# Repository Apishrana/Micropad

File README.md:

# Macropad

This is my macropad that i am gonna be using to increase my productivity,
[Design link](https://www.tldraw.com/f/6q5K0vjcdTGi3-sUILjF2?d=v49.-201.1104.759.page)

## Why i made this

This macropad have all the shortcuts that I commonly use in my coding and research these are located on left side of the macropad, on the right side I have music control and display I am gonna be using it on study sessions so i don't have to look on my screen to control music

## Project images

### Full assembly

### PCB

### Schematic

## BOM

check [BOM](./BOM.csv)

## Author

Created by [ApishRana](https://github.com/ApishRana)

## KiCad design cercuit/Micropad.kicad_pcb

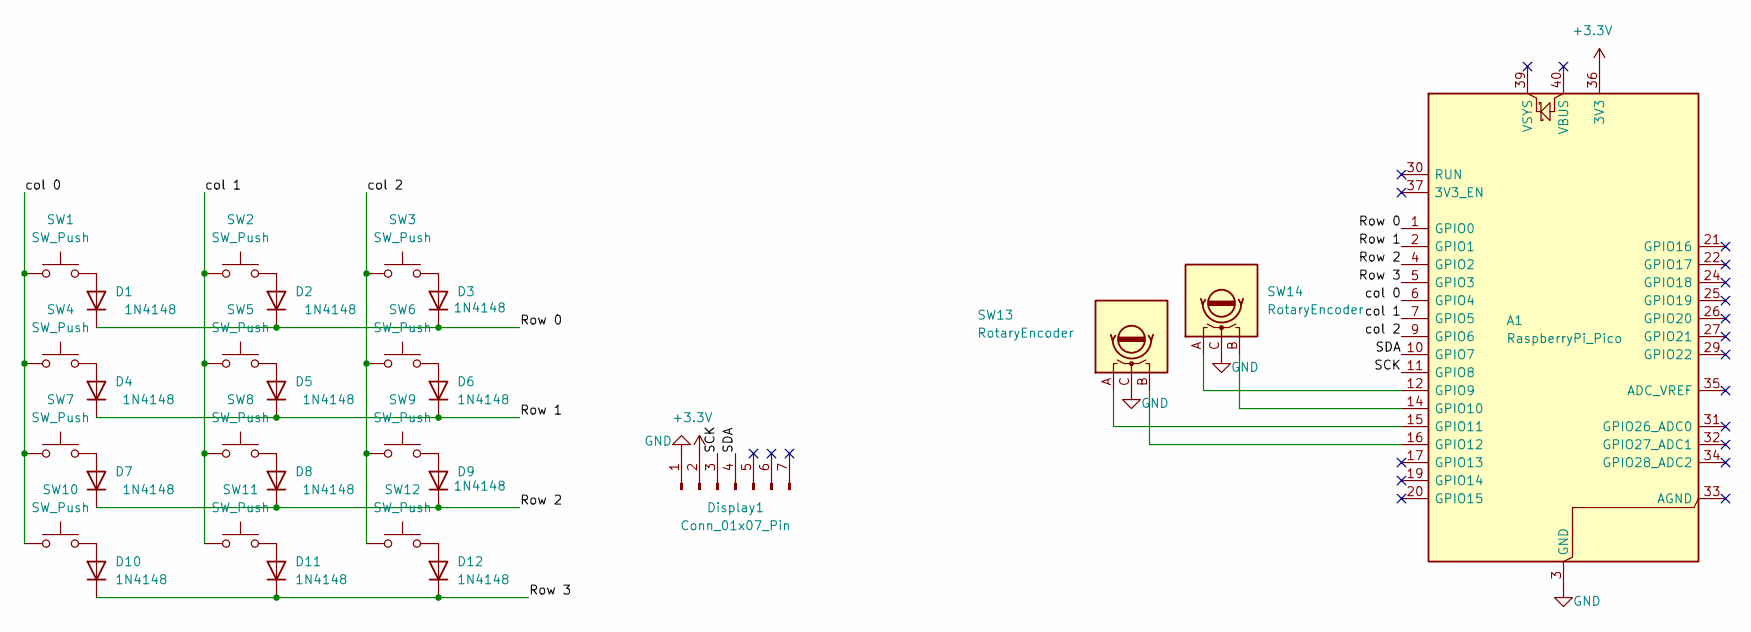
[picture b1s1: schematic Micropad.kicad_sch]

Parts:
A1: RaspberryPi_Pico; RaspberryPi_Pico_Common_THT
D1, D2, D3, D4, D5, D6, D7, D8, D9, D10, D11, D12: 1N4148; D_DO-35_SOD27_P7.62mm_Horizontal
Display1: Conn_01x07_Pin; 128x64OLED
SW1, SW2, SW3, SW4, SW5, SW6, SW7, SW8, SW9, SW10, SW11, SW12: SW_Push; SW_Cherry_MX_1.00u_PCB
SW13, SW14: RotaryEncoder; RotaryEncoder_Alps_EC11E-Switch_Vertical_H20mm

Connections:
+3.3V: A1.36 (3V3), Display1.2
/Row 0: A1.1 (GPIO0), D1.1 (K), D2.1 (K), D3.1 (K)
/Row 1: A1.2 (GPIO1), D4.1 (K), D5.1 (K), D6.1 (K)
/Row 2: A1.4 (GPIO2), D7.1 (K), D8.1 (K), D9.1 (K)
/Row 3: A1.5 (GPIO3), D10.1 (K), D11.1 (K), D12.1 (K)
/SCK: A1.11 (GPIO8), Display1.3
/SDA: A1.10 (GPIO7), Display1.4
/col 0: A1.6 (GPIO4), SW1.1, SW4.1, SW7.1, SW10.1
/col 1: A1.7 (GPIO5), SW2.1, SW5.1, SW8.1, SW11.1
/col 2: A1.9 (GPIO6), SW3.1, SW6.1, SW9.1, SW12.1
GND: A1.3 (GND), A1.8 (GND), A1.13 (GND), A1.18 (GND), A1.23 (GND), A1.28 (GND), A1.38 (GND), Display1.1, SW13.C, SW14.C
unnamed: A1.12 (GPIO9), SW14.A
unnamed: A1.14 (GPIO10), SW14.B
unnamed: A1.15 (GPIO11), SW13.A
unnamed: A1.16 (GPIO12), SW13.B
unnamed: D1.2 (A), SW1.2
unnamed: D2.2 (A), SW2.2
unnamed: D3.2 (A), SW3.2
unnamed: D4.2 (A), SW4.2
unnamed: D5.2 (A), SW5.2
unnamed: D6.2 (A), SW6.2
unnamed: D7.2 (A), SW7.2
unnamed: D8.2 (A), SW8.2
unnamed: D9.2 (A), SW9.2
unnamed: D10.2 (A), SW10.2
unnamed: D11.2 (A), SW11.2
unnamed: D12.2 (A), SW12.2

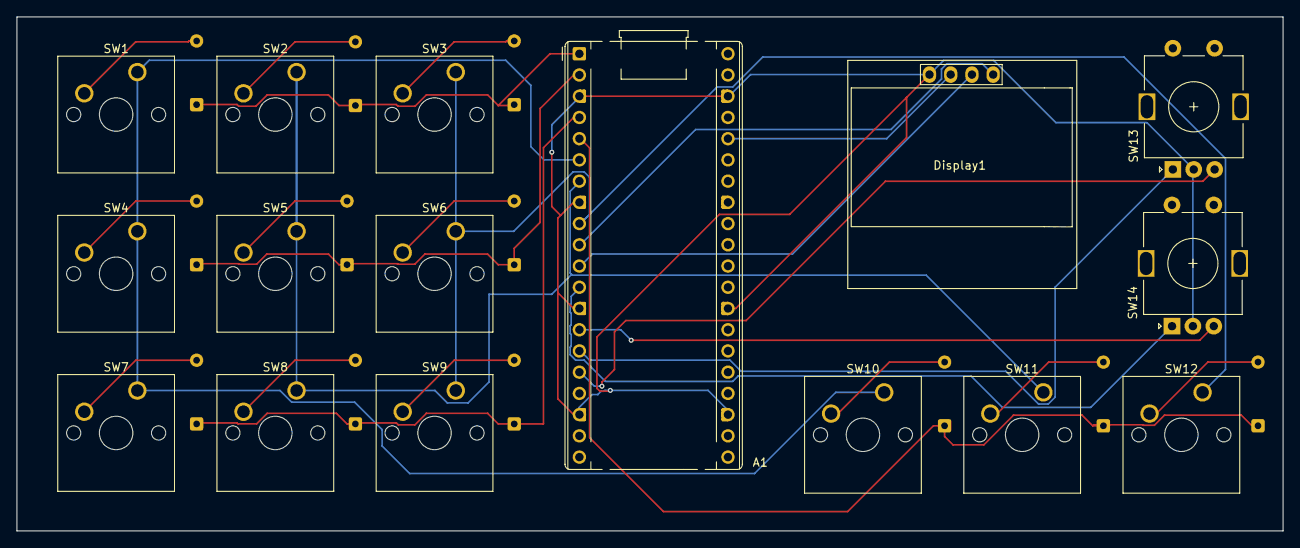
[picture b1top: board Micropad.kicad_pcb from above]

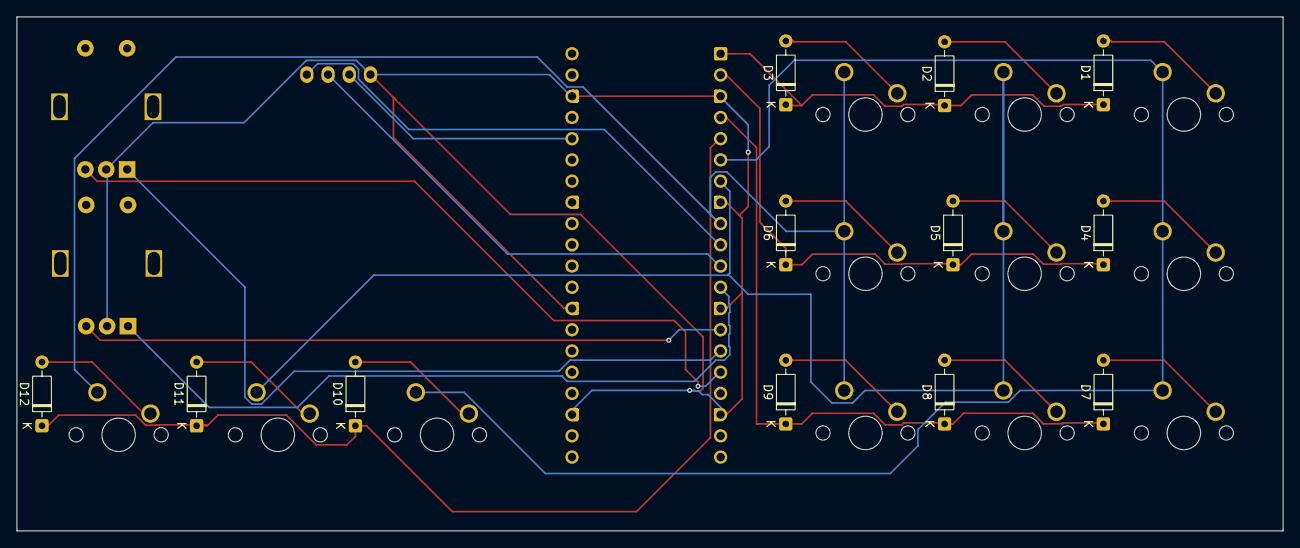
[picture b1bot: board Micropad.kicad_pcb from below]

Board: 2 copper layers, 151.5 x 61.5 mm, 28 parts (12 on the bottom side), 27 nets.
